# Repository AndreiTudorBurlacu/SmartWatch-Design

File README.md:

# Design Smartwatch

A smartwatch based on the Nordic nRF52840 microcontroller with an e-Paper display.
---

## Diagrama bloc

---

## Bill of Materials

| Ref | Componenta | Valoare | JLC Parts | Datasheet |
|-----|------------|---------|-----------|-----------|
| U1 | nRF52840 | $5.12   | [JLC](https://jlcpcb.com/parts/componentSearch?searchTxt=nRF52840-QF) | [DS](https://jlcpcb.com/api/file/downloadByFileSystemAccessId/8589839228197629952) |
| X1 | NX2016SA-32MHZ-EXS00A-CS11336 | $9.06   | [JLC](https://jlcpcb.com/partdetail/NDK-NX2016SA_32MHZ_EXS00ACS11336/C6134317) | [DS](https://jlcpcb.com/api/file/downloadByFileSystemAccessId/8603064888214908928) |
| X2 | FC-135_32.7680KA-A3 | $0.2923 | [JLC](https://jlcpcb.com/partdetail/SeikoEpson-FC_135_32_7680KAA3/C2650472) | [DS](https://jlcpcb.com/partdetail/SeikoEpson-FC_135_32_7680KAA3/C2650472) |
| L2 | RC0402JR-070RL | $0.02   | [JLC](https://jlcpcb.com/partdetail/YAGEO-RC0402JR070RL/C60485) | [DS](https://jlcpcb.com/api/file/downloadByFileSystemAccessId/8717146932348461056) |
| L3 | RC0402JR-070RL | $0.01   | [JLC](https://jlcpcb.com/partdetail/YAGEO-RC0402JR070RL/C60485) | [DS](https://jlcpcb.com/api/file/downloadByFileSystemAccessId/8717146932348461056) |
| L5 | 744043680 | $9.33   | [JLC](https://jlcpcb.com/partdetail/WurthElektronik-744043680/C2045671) | [DS](https://www.we-online.com/components/products/datasheet/744043680.pdf) |
| L7 | MLP2016SR47MT0S1 | $0.9    | [JLC](https://jlcpcb.com/partdetail/TDK-MLP2016SR47MT0S1/C87545) | [DS](https://jlcpcb.com/api/file/downloadByFileSystemAccessId/8588933367512879104) |
| IC1 | BQ25180YBGR | $2.04   | [JLC](https://jlcpcb.com/partdetail/TexasInstruments-BQ25180YBGR/C3682423) | [DS](https://www.ti.com/cn/lit/gpn/bq25180) |
| IC2 | DRV2605YZFR | $1.61   | [JLC](https://jlcpcb.com/partdetail/TexasInstruments-DRV2605YZFR/C81079) | [DS](https://www.ti.com/cn/lit/gpn/drv2605) |
| IC3 | BMA423 | $12.30  | [JLC](https://jlcpcb.com/partdetail/BoschSensortec-BMA423/C189517) | [DS](https://jlcpcb.com/api/file/downloadByFileSystemAccessId/8588894317147017216) |
| IC9 | RT6160 | $0.46   | [JLC](https://jlcpcb.com/partdetail/RichtekTech-RT6160AWSC/C7065276) | [DS](https://jlcpcb.com/api/file/downloadByFileSystemAccessId/8600398231234883584) |
| ANT1 | 2450AT18B100E | $1.04   | [JLC](https://jlcpcb.com/partdetail/JohansonDielectrics-2450AT18B100E/C2917717) | [DS](https://jlcpcb.com/api/file/downloadByFileSystemAccessId/8588940948130156544) |
| D2 | MBR0530 | $0.02   | [JLC](https://jlcpcb.com/partdetail/78464-MBR0530/C77336) | [DS](https://jlcpcb.com/api/file/downloadByFileSystemAccessId/8586175081181818880) |
| D3 | USBLC6-2SC6Y | $0.23   | [JLC](https://jlcpcb.com/partdetail/STMicroelectronics-USBLC62SC6Y/C2969755) | [DS](https://jlcpcb.com/api/file/downloadByFileSystemAccessId/8603165824304111616) |
| D4 | MBR0530 | $0.03   | [JLC](https://jlcpcb.com/partdetail/78464-MBR0530/C77336) | [DS](https://jlcpcb.com/api/file/downloadByFileSystemAccessId/8586175081181818880) |
| D5 | MBR0530 | $0.04   | [JLC](https://jlcpcb.com/partdetail/78464-MBR0530/C77336) | [DS](https://jlcpcb.com/api/file/downloadByFileSystemAccessId/8586175081181818880) |
| Q1 | DMG2305UX-7 | $0.15   | [JLC](https://jlcpcb.com/partdetail/DiodesIncorporated-DMG2305UX7/C150470) | [DS](https://jlcpcb.com/api/file/downloadByFileSystemAccessId/8560079443617075200) |
| Q3 | SI1308EDL-T1-GE3 | $0.15   | [JLC](https://jlcpcb.com/partdetail/VishayIntertech-SI1308EDL_T1GE3/C469327) | [DS](https://jlcpcb.com/api/file/downloadByFileSystemAccessId/8588884784742846464) |
| J1 | 503480-2400 | $0.67   | [JLC](https://jlcpcb.com/partdetail/MOLEX-5034802400/C122434) | [DS](https://www.molex.com/content/dam/molex/molex-dot-com/products/automated/en-us/salesdrawingpdf/503/503480/5034802400_sd.pdf?inline) |
| J4 | KH-TYPE-C-16P | $0.05   | [JLC](https://jlcpcb.com/partdetail/Shenzhen_KinghelmElec-KH_TYPE_C16P/C709357) | [DS](https://jlcpcb.com/api/file/downloadByFileSystemAccessId/8588905154556923904) |
| U3 | MAX17048G-T10 | $2.76   | [JLC](https://jlcpcb.com/partdetail/2777647-MAX17048GT10/C2682616) | [DS](https://jlcpcb.com/api/file/downloadByFileSystemAccessId/8588907428524003328) |
| SWD | TC2030-IDC | $101.26 | [JLC](https://jlcpcb.com/partdetail/MicrochipTech-TC2030_CLIP3PACK/C5444772) | [DS](https://www.lcsc.com/datasheet/lcsc_datasheet_2403201318_Microchip-Tech-TC2030-CLIP-3PACK_C5444772.pdf) |

---

## Descriere Functionalitati Hardware

### Microcontroller - nRF52840

Arhitectura:
- Procesor ARM Cortex-M4 cu FPU ruland la 64 MHz
- 1 MB memorie Flash si 256 KB RAM
- Suport nativ pentru Bluetooth 5, Bluetooth Low Energy (BLE), Thread si Zigbee
- Dispune de USB 2.0 (Full Speed), SPI, I2C, UART si QSPI
 
### Display E-Paper - Waveshare 1.54" V2
 
Display-ul comunica prin SPI pe 4 fire:
- Rezolutie: 200x200 pixeli
- Interfata comunicare: SPI
- Consum de energie ultra-redus; consuma aproximativ 26.4 mW doar in timpul reimprospatarii si scade sub 0.01 uA in modul standby
- Suporta partial refresh (reimprospatarea doar a unei anumite zone din ecran)
 
### IMU - BMA423
 
Accelerometrul BMA423 comunica prin I2C:

- Tip senzor: Accelerometru digital pe 3 axe.
- Rezolutie date - 12 biti
- Interfete comunicare: I2C si SPI
- Consum foarte eficient, trage in jur de 14 uA cand se afla in modul activ de numarare a pasilor
 
### Incarcator Baterie - BQ25180

- Dimensiuni: 32.5mm x 21mm x 5.5mm
- Curent de incarcare: Flexibil, poate incarca de la cativa miliamperi pana la 1 A
- Interfata control: Comunicare I2C prin care procesorul principal poate citi statusul bateriei si poate modifica parametrii de incarcare din mers
- Tensiune standard de intrare de 5V, dar are protectie la supratensiune (OVP) care rezista pana la 25V
 
### Baterie - AKYGA LP502030
 
- Tensiune - 3.7V nominal (ajunge la 4.2V cand este incarcata 100% si scade spre 3.0V cand este descarcata)
- Capacitate: Aproximativ 250 mAh
- Dimensiuni - 5 mm x 20 mm x 30 mm
 
### Motor Vibratii - FIT0774

- Tensiune de operare: 3V curent continuu
- Curent maxim consumat - 85 mA in momentul in care vibreaza la capacitate maxima
- Viteza de rotatie: Aproximativ 12000 RPM
- 10 mm diametru si o grosime de doar 2.7 mm
 
### Conector Debug - TC2030-IDC
 
- Tip contact: 6 pini cu arc (pogo-pins) dispusi pe 2 randuri, cu o distanta de 1.27 mm intre ei
- Folosit pentru programare si debugging SWD
- Semnale: SWDIO, SWDCLK, GND, VCC, RESET
 
---
 
## Pinii nRF52840
 
| Pin nRF52840 | Semnal | Componenta | Interfata |
|--------------|--------|-----------|-----------|
| P0.00/XL1 | XL1 | Crystal X2 (32.768kHz) | XTAL |
| P0.01/XL2 | XL2 | Crystal X2 (32.768kHz) | XTAL |
| P0.05/AIN3 | EPD_CS | E-Paper (J1 FPC) | SPI CS |
| P0.06 | SDA | BMA423, BQ25180, MAX17048, DRV2605 | I2C SDA |
| P0.07 | SCL | BMA423, BQ25180, MAX17048, DRV2605 | I2C SCL |
| P0.08 | IMU_INT1 | BMA423 | GPIO Input |
| P1.08 | IMU_INT2 | BMA423 | GPIO Input |
| P0.11 | PMIC_INT | BQ25180 | GPIO Input |
| P0.12 | HAPTIC_EN | DRV2605 | GPIO |
| VBUS | VBUS | USB-C (J4) | Power |
| D- | D- | USB-C (J4) / USBLC6 | USB |
| D+ | D+ | USB-C (J4) / USBLC6 | USB |
| P0.13 | SW_UP | Buton Up | GPIO Input |
| P0.14 | SW_ENT | Buton Enter | GPIO Input |
| P0.15 | EPD_DC | E-Paper (J1 FPC) | SPI DC |
| P0.16 | EPD_RST | E-Paper (J1 FPC) | GPIO |
| P0.17 | EPD_BUSY | E-Paper (J1 FPC) | GPIO Input |
| P0.18/RESET | RESET | TC2030-IDC | SWD/GPIO |
| SWDCLK | SWDCLK | TC2030-IDC | SWD |
| SWDIO | SWDIO | TC2030-IDC | SWD |
| P1.02 | SW_DN | Buton Down | GPIO Input |
| P0.10/NFC2 | ALERT | MAX17048 | GPIO Input |
| ANT | RF | Antena 2450AT18B100E | RF |
| P0.02/AIN0 | SCK | E-Paper (J1 FPC) | SPI SCK |
| P0.03/AIN1 | MOSI | E-Paper (J1 FPC) | SPI MOSI |

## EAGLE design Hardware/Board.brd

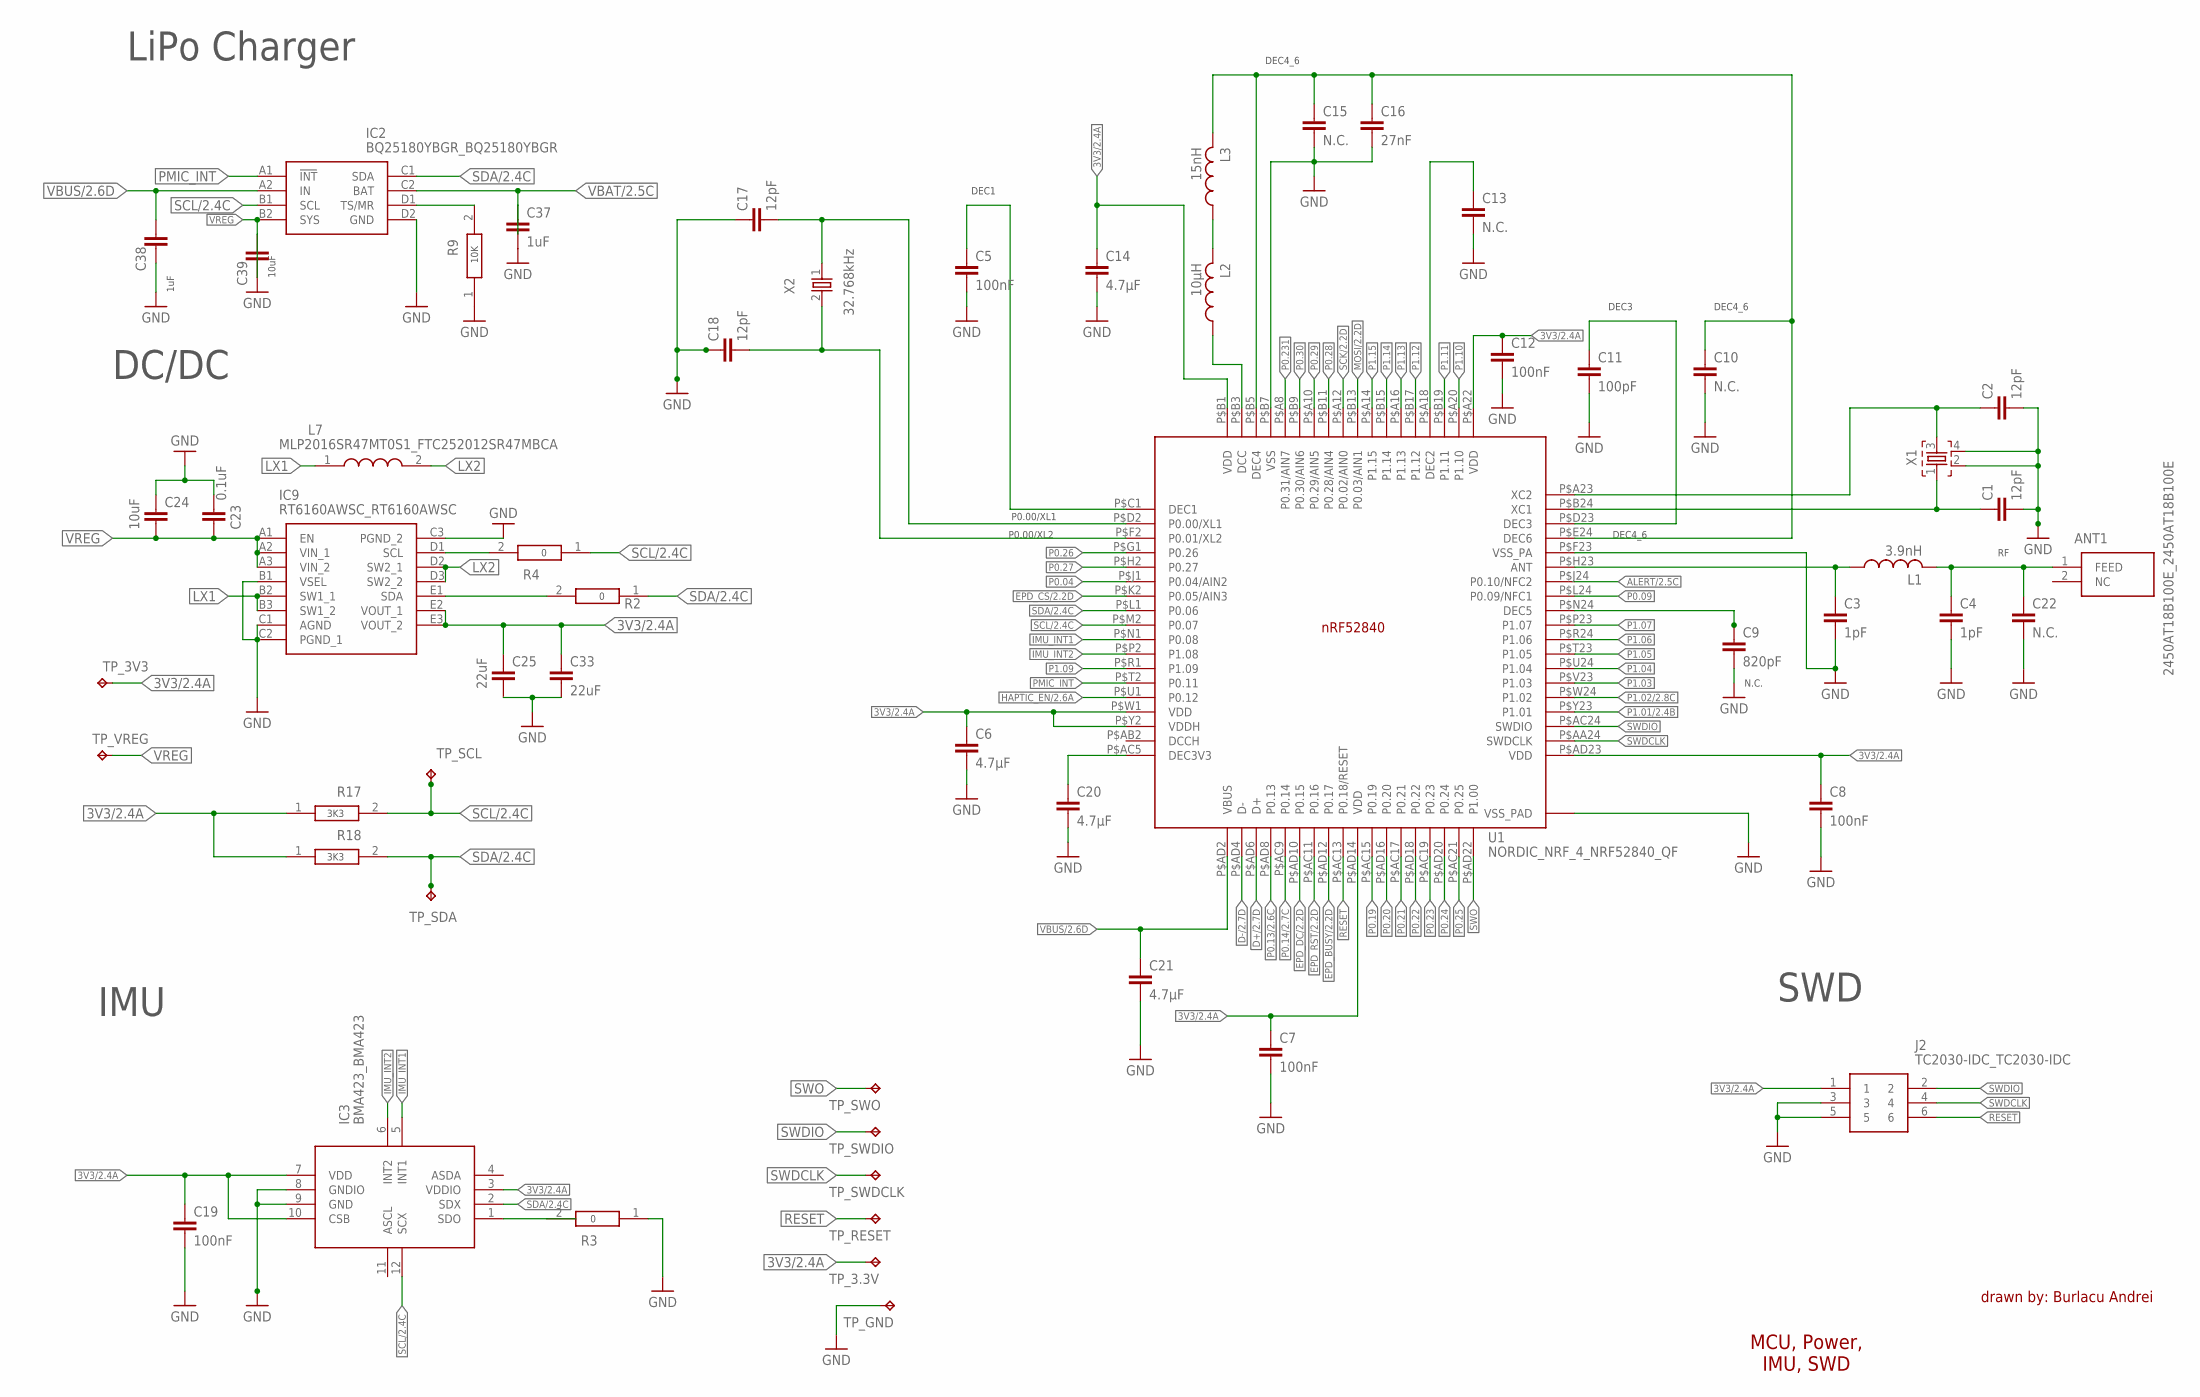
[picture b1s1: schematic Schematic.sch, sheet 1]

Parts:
ANT1: 2450AT18B100E_2450AT18B100E; 2450AT18B100E_ANTC3216X140N
C1, C2, C17, C18: 12pF; NORDIC_NRF_3_RESC0201_L
C3, C4: 1pF; NORDIC_NRF_3_RESC0201_L
C5, C7, C8, C12, C19: 100nF; NORDIC_NRF_3_RESC0201_L
C6, C14, C20, C21: 4.7µF; NORDIC_NRF_3_RESC0201_L
C9: 820pF; NORDIC_NRF_3_RESC0201_L
C10, C13, C15, C22: N.C.; NORDIC_NRF_3_RESC0201_L
C11: 100pF; NORDIC_NRF_3_RESC0201_L
C16: 27nF; NORDIC_NRF_3_RESC0201_L
C23: 0.1uF; NORDIC_NRF_3_RESC0201_L
C24: 10uF; NORDIC_NRF_3_RESC0201_L
C25, C33: 22uF; NORDIC_NRF_3_RESC0201_L
C37: 1uF; NORDIC_NRF_3_RESC0201_L
C38, C39: NORDIC_NRF_3_CAPACITOR_0201_L; NORDIC_NRF_3_RESC0201_L
IC2: BQ25180YBGR_BQ25180YBGR; BQ25180YBGR_BGA8C40P2X4_100X155X50
IC3: BMA423_BMA423
IC9: RT6160AWSC_RT6160AWSC; RT6160AWSC_BGA15C40P3X5_140X230X60
J2: TC2030-IDC_TC2030-IDC; TC2030-IDC_TC2030IDC
L1: 3.9nH; NORDIC_NRF_2_RESC0402_L
L2: 10µH; NORDIC_NRF_2_RESC0402_L
L3: 15nH; NORDIC_NRF_2_RESC0402_L
L7: MLP2016SR47MT0S1_FTC252012SR47MBCA; MLP2016SR47MT0S1_INDC2016X100N
R2, R3, R4, R9, R17, R18: ERA-1AEB3401C_CPF0201D7K68C1; ERA-1AEB3401C_0201
TP_3.3V, TP_3V3: HECTOR_WATCH_1_TPTP20R; HECTOR_WATCH_1_TP20R
TP_GND: HECTOR_WATCH_1_TPTP20R; HECTOR_WATCH_1_TP20R
TP_RESET: HECTOR_WATCH_1_TPTP20R; HECTOR_WATCH_1_TP20R
TP_SCL: HECTOR_WATCH_1_TPTP20R; HECTOR_WATCH_1_TP20R
TP_SDA: HECTOR_WATCH_1_TPTP20R; HECTOR_WATCH_1_TP20R
TP_SWDCLK: HECTOR_WATCH_1_TPTP20R; HECTOR_WATCH_1_TP20R
TP_SWDIO: HECTOR_WATCH_1_TPTP20R; HECTOR_WATCH_1_TP20R
TP_SWO: HECTOR_WATCH_1_TPTP20R; HECTOR_WATCH_1_TP20R
TP_VREG: HECTOR_WATCH_1_TPTP20R; HECTOR_WATCH_1_TP20R
U1: NORDIC_NRF_4_NRF52840_QF; NORDIC_NRF_4_AQFN50P700X700X85_HS-74N
X1: NORDIC_NRF_XTAL_32MHZ; NORDIC_NRF_BT-XTAL_2016_N
X2: 32.768kHz; NORDIC_NRF_1_XTAL_3215_N

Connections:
GND: C3.2, C4.2, C5.2, C6.2, C7.2, C8.2, C9.2, C10.2, C11.2, C12.2, C13.2, C14.2, C15.2, C16.2, C19.2, C20.2, C21.2, C22.2, C23.1, C24.1, C25.2, C33.2, C37.2, C38.2, C39.1, C39.2, IC2.B2 (SYS), IC2.D2 (GND), IC9.B1 (VSEL), IC9.C1 (AGND), IC9.C2 (PGND_1), IC9.C3 (PGND_2), J2.3, J2.5, R3.1, R9.1, TP_GND.TP, U1.P$74 (VSS_PAD), U1.P$75 (VSS_PAD), U1.P$76 (VSS_PAD), U1.P$77 (VSS_PAD), U1.P$78 (VSS_PAD), U1.P$79 (VSS_PAD), U1.P$80 (VSS_PAD), U1.P$81 (VSS_PAD), U1.P$82 (VSS_PAD), U1.P$83 (VSS_PAD), U1.P$84 (VSS_PAD), U1.P$85 (VSS_PAD), U1.P$86 (VSS_PAD), U1.P$87 (VSS_PAD), U1.P$88 (VSS_PAD), U1.P$89 (VSS_PAD), U1.P$90 (VSS_PAD), U1.P$B7 (VSS), U1.P$F23 (VSS_PA); also elsewhere on the board
unnamed: IC2.D1 (TS/MR), R9.2
unnamed: C38.1, IC2.A2 (IN)
unnamed: C37.1, IC2.C2 (BAT)
unnamed: C23.2, C24.2, IC9.A1 (EN), IC9.A2 (VIN_1), IC9.A3 (VIN_2)
unnamed: IC9.B2 (SW1_1), IC9.B3 (SW1_2)
unnamed: IC9.D1 (SCL), R4.2
unnamed: R17.1, R18.1
unnamed: IC9.D2 (SW2_1), IC9.D3 (SW2_2)
unnamed: C25.1, C33.1, IC9.E2 (VOUT_1), IC9.E3 (VOUT_2)
unnamed: IC9.E1 (SDA), R2.2
unnamed: C19.1, IC3.7 (VDD), IC3.10 (CSB)
unnamed: IC3.8 (GNDIO), IC3.9 (GND)
unnamed: IC3.1 (SDO), R3.2
unnamed: C7.1, U1.P$AD14 (VDD)
unnamed: C21.1, U1.P$AD2 (VBUS)
unnamed: C8.1, U1.P$AD23 (VDD)
unnamed: C3.1, L1.1, U1.P$H23 (ANT)
unnamed: ANT1.1 (FEED), C4.1, C22.1, L1.2
unnamed: C10.1, C15.1, C16.1, L3.2, U1.P$B5 (DEC4), U1.P$E24 (DEC6)
unnamed: C11.1, U1.P$D23 (DEC3)
unnamed: C1.1, U1.P$B24 (XC1), X1.1
unnamed: C2.1, U1.P$A23 (XC2), X1.3
unnamed: C1.2, C2.2, X1.2, X1.4
unnamed: C12.1, U1.P$A22 (VDD)
unnamed: C13.1, U1.P$A18 (DEC2)
unnamed: L2.2, L3.1
unnamed: L2.1, U1.P$B3 (DCC)
unnamed: C20.1, U1.P$AC5 (DEC3V3)
unnamed: C6.1, U1.P$W1 (VDD), U1.P$Y2 (VDDH)
unnamed: C14.1, U1.P$B1 (VDD)
unnamed: C5.1, U1.P$C1 (DEC1)
unnamed: C17.2, U1.P$D2 (P0.00/XL1), X2.1
unnamed: C18.2, U1.P$F2 (P0.01/XL2), X2.2
SDA/2.4C: IC2.C1 (SDA)

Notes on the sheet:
LiPo Charger
10K
DC/DC
3K3
10uF
1uF
IMU
N.C.
DEC3
DEC4_6
DEC1
P0.00/XL1
P0.00/XL2
drawn by: Burlacu Andrei
MCU, Power, IMU, SWD
SWD

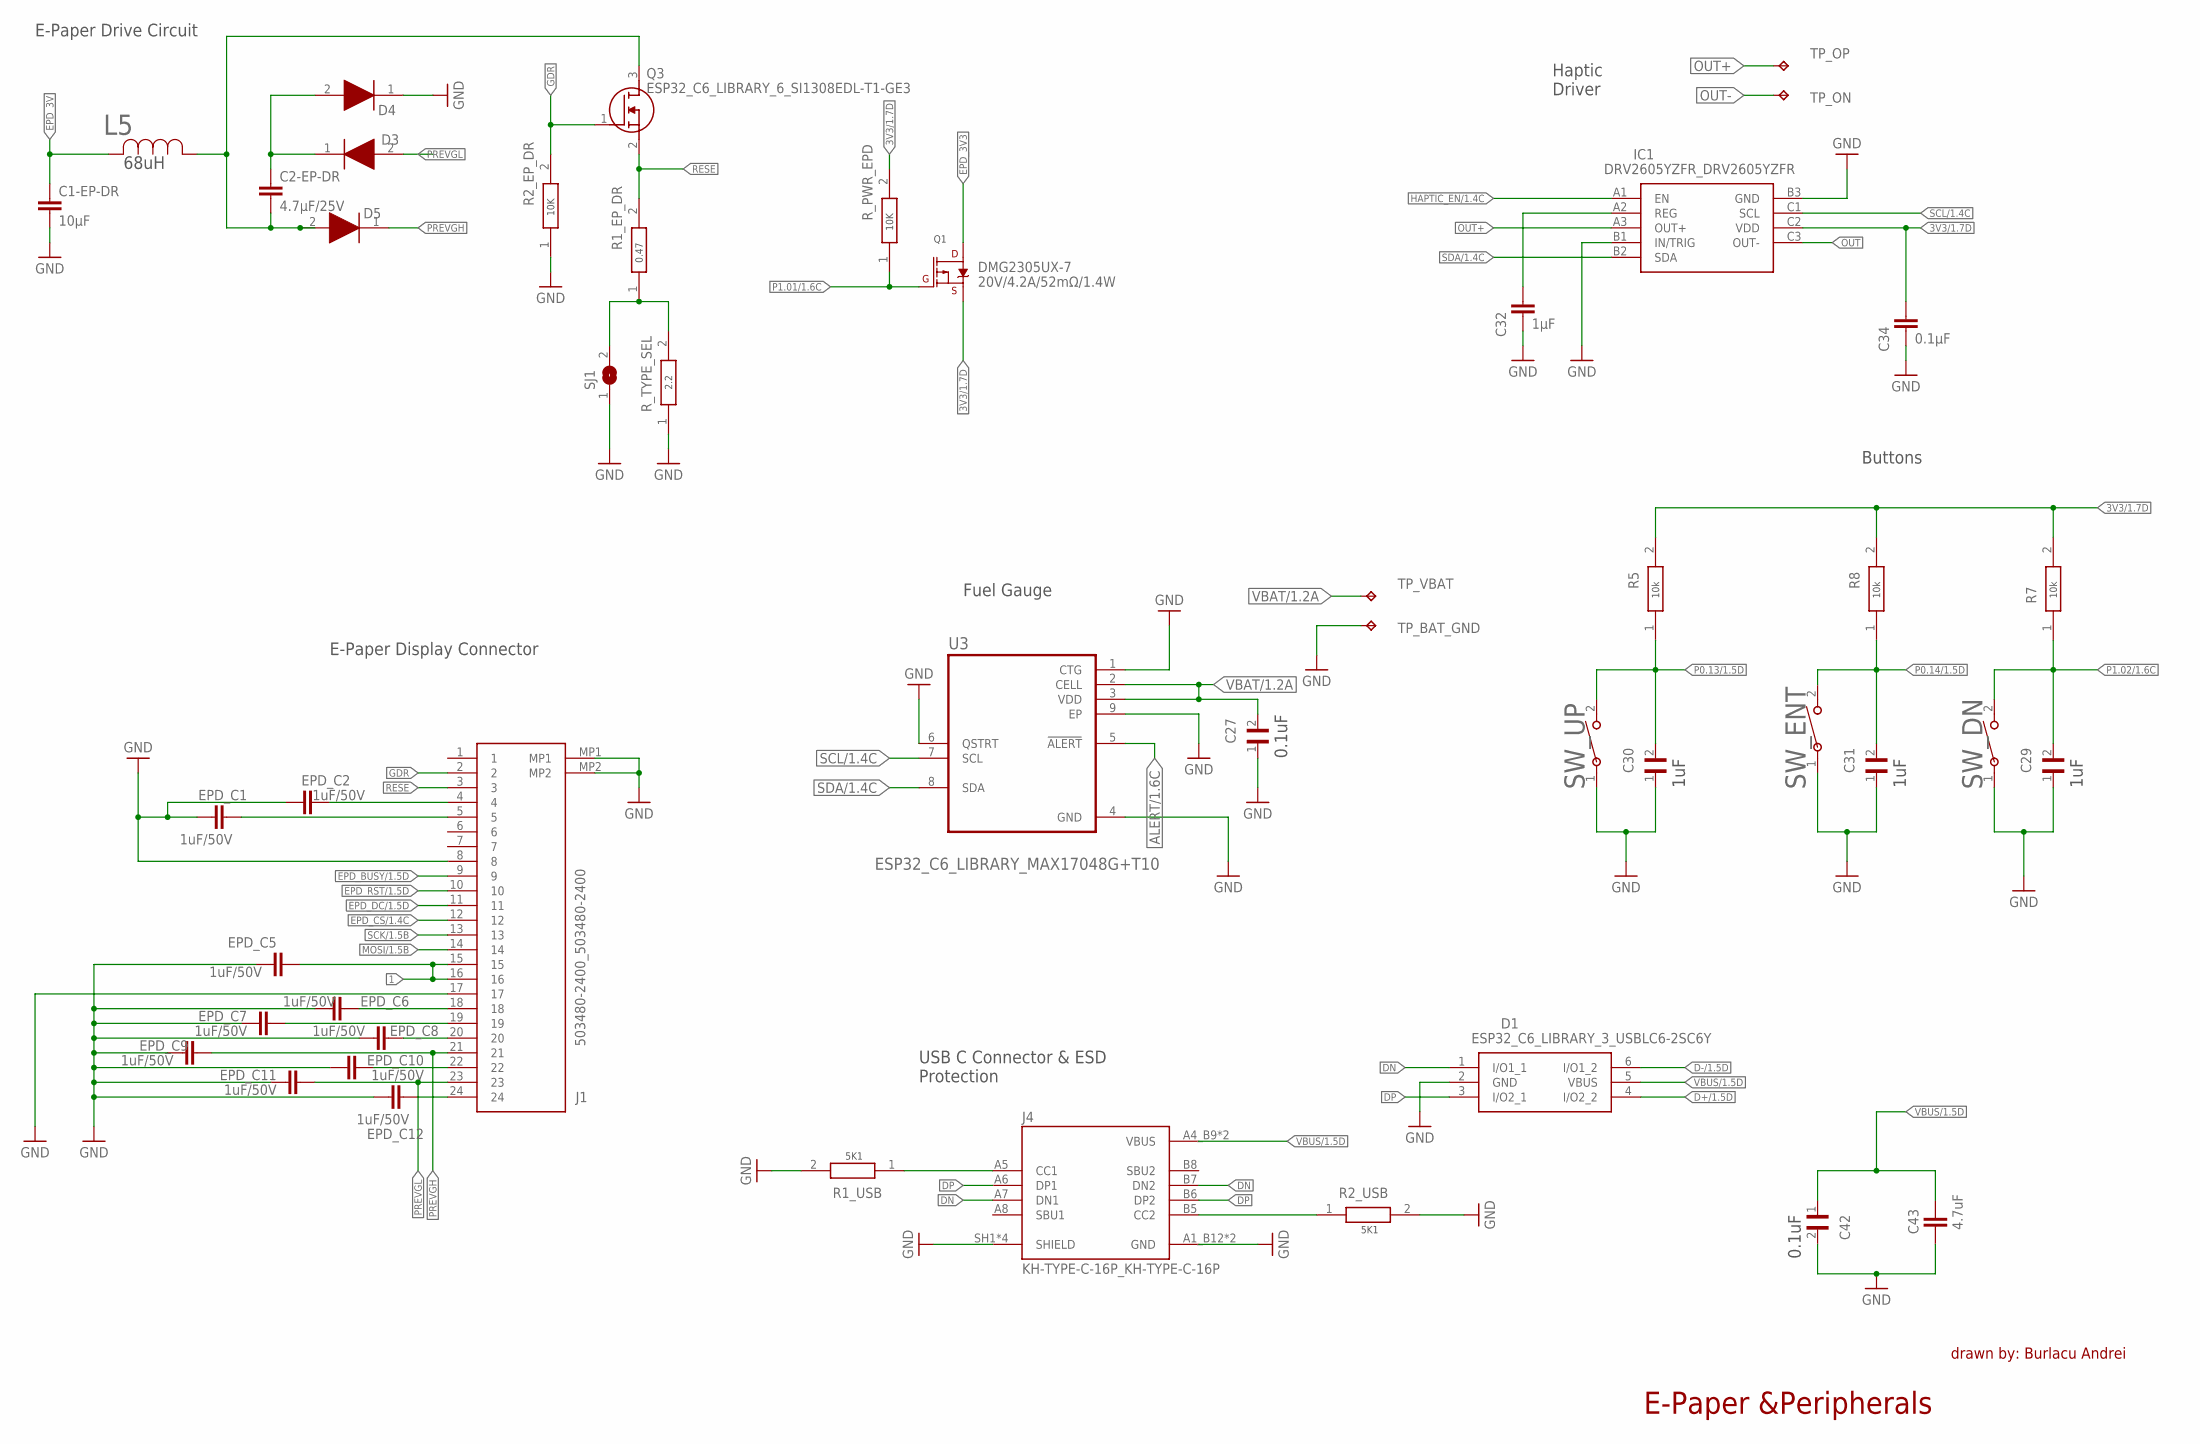
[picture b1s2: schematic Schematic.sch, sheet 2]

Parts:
C1-EP-DR: 10µF; NORDIC_NRF_3_RESC0201_L
C2-EP-DR: 4.7µF/25V; NORDIC_NRF_3_RESC0201_L
C27, C29, C30, C31, C42: GRM011R60J152KE01L_2_GRM011R60J152KE01L; GRM011R60J152KE01L_2_CAPC0201X13N
C32: 1µF; NORDIC_NRF_3_RESC0201_L
C34: 0.1µF; NORDIC_NRF_3_RESC0201_L
C43: 4.7uF; NORDIC_NRF_3_RESC0201_L
D1: ESP32_C6_LIBRARY_3_USBLC6-2SC6Y; ESP32_C6_LIBRARY_3_SOT95P280X145-6N
D3, D4, D5: ESP32_C6_LIBRARY_5_MBR0530; ESP32_C6_LIBRARY_5_SOD3716X135N
DMG2305UX-7: 20V/4.2A/52mΩ/1.4W; ESP32_C6_LIBRARY_4_ESP32_C6_LIBRARY_4_ESP32_C6_LIBRARY_4_ES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
EPD_C1, EPD_C2, EPD_C5, EPD_C6, EPD_C7, EPD_C8, EPD_C9, EPD_C10, EPD_C11, EPD_C12: 1uF/50V; NORDIC_NRF_3_RESC0201_L
IC1: DRV2605YZFR_DRV2605YZFR; DRV2605YZFR_BGA9C50P3X3_144X144X62
J1: 503480-2400_503480-2400; 503480-2400_5034802400
J4: KH-TYPE-C-16P_KH-TYPE-C-16P; KH-TYPE-C-16P_KINGHELM_KH-TYPE-C-16P
L5: 68uH; ESP32_C6_LIBRARY_2_IND_4828-WE-TPC_WRE
Q3: ESP32_C6_LIBRARY_6_SI1308EDL-T1-GE3; ESP32_C6_LIBRARY_6_SOT65P210X110-3N
R1_EP_DR, R1_USB, R2_EP_DR, R2_USB, R5, R7, R8: ERA-1AEB3401C_CPF0201D7K68C1; ERA-1AEB3401C_0201
R_PWR_EPD: ERA-1AEB3401C_CPF0201D7K68C1; ERA-1AEB3401C_0201
R_TYPE_SEL: ERA-1AEB3401C_CPF0201D7K68C1; ERA-1AEB3401C_0201
SJ1: ESP32_C6_LIBRARY_7_JUMPER_SJ
SW_DN: 2025-10-22_07-23-44_LIBRARY_EVP-AKE31ASW_EVP-AKE3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; 2025-10-22_07-23-44_LIBRARY_SW_EVP-AKE31A_PAN
SW_ENT: 2025-10-22_07-23-44_LIBRARY_EVP-AKE31ASW_EVP-AKE3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; 2025-10-22_07-23-44_LIBRARY_SW_EVP-AKE31A_PAN
SW_UP: 2025-10-22_07-23-44_LIBRARY_EVP-AKE31ASW_EVP-AKE3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; 2025-10-22_07-23-44_LIBRARY_SW_EVP-AKE31A_PAN
TP_BAT_GND: HECTOR_WATCH_1_TPTP20R; HECTOR_WATCH_1_TP20R
TP_ON: HECTOR_WATCH_1_TPTP20R; HECTOR_WATCH_1_TP20R
TP_OP: HECTOR_WATCH_1_TPTP20R; HECTOR_WATCH_1_TP20R
TP_VBAT: HECTOR_WATCH_1_TPTP20R; HECTOR_WATCH_1_TP20R
U3: ESP32_C6_LIBRARY_MAX17048G+T10; ESP32_C6_LIBRARY_SON50P200X200X80-9N

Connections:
GND: C1-EP-DR.2, C27.1, C29.1, C30.1, C31.1, C32.2, C34.2, D1.2 (GND), D4.1 (K), EPD_C1.1, EPD_C2.1, EPD_C5.1, EPD_C6.1, EPD_C7.1, EPD_C8.1, EPD_C9.1, EPD_C10.1, EPD_C11.1, EPD_C12.1, IC1.B1 (IN/TRIG), IC1.B3 (GND), J1.8, J1.17, J1.MP1, J1.MP2, J4.A1_B12 (GND), J4.A12_B1 (GND), J4.SH1 (SHIELD), J4.SH2 (SHIELD), J4.SH3 (SHIELD), J4.SH4 (SHIELD), R1_USB.2, R2_EP_DR.1, R2_USB.2, R_TYPE_SEL.1, SJ1.1, SW_DN.1, SW_ENT.1, SW_UP.1, TP_BAT_GND.TP, U3.1 (CTG), U3.4 (GND), U3.6 (QSTRT), U3.9 (EP); also elsewhere on the board
GND1: R1_EP_DR.1, R_TYPE_SEL.2, SJ1.2
GND2: C29.2, R7.1, SW_DN.2
GND3: C31.2, R8.1, SW_ENT.2
GND4: C30.2, R5.1, SW_UP.2
unnamed: C1-EP-DR.1, L5.2
unnamed: C2-EP-DR.2, D5.2 (A), L5.1, Q3.3 (D)
unnamed: C2-EP-DR.1, D3.1 (K), D4.2 (A)
unnamed: Q3.1 (G), R2_EP_DR.2
unnamed: Q3.2 (S), R1_EP_DR.2
unnamed: DMG2305UX-7.1 (G), R_PWR_EPD.1
unnamed: C32.1, IC1.A2 (REG)
unnamed: C34.1, IC1.C2 (VDD)
unnamed: R5.2, R7.2, R8.2
unnamed: C27.2, U3.2 (CELL), U3.3 (VDD)
unnamed: EPD_C12.2, J1.24
unnamed: EPD_C2.2, J1.4
unnamed: EPD_C1.2, J1.5
unnamed: EPD_C5.2, J1.15, J1.16
unnamed: EPD_C11.2, J1.23
unnamed: EPD_C10.2, J1.22
unnamed: EPD_C9.2, J1.21
unnamed: EPD_C8.2, J1.20
unnamed: EPD_C7.2, J1.19
unnamed: EPD_C6.2, J1.18
unnamed: J4.A4_B9 (VBUS), J4.A9_B4 (VBUS)
unnamed: J4.B5 (CC2), R2_USB.1
unnamed: J4.A5 (CC1), R1_USB.1
unnamed: C42.2, C43.1
unnamed: C42.1, C43.2

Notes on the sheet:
E-Paper Drive Circuit
10K
0.47
2.2
68uH
Haptic Driver
Buttons
10k
1uF
Fuel Gauge
0.1uF
E-Paper Display Connector
USB C Connector & ESD Protection
5K1
E-Paper &Peripherals
drawn by: Burlacu Andrei

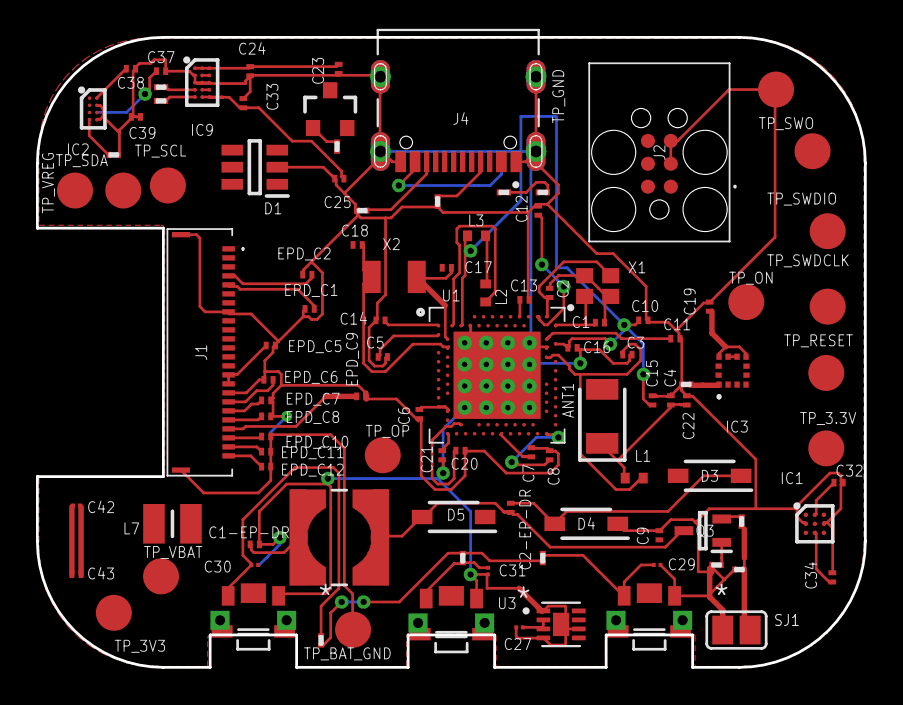
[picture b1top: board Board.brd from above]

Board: 2 copper layers, 46.0 x 35.0 mm, 105 parts (0 on the bottom side), 63 nets.

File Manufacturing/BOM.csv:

Reference Designators;Quantity;Description;Package;Value;Manufacturer;Manufacturer Part Number;Vendor;Vendor Part Number;Top/Bottom;
;1;PCB Board;Board;;;;;;;
ANT1;1;Antennas 2.45GHz ANTENNA;2450AT18B100E_ANTC3216X140N;2450AT18B100E_2450AT18B100E;;;;;Top;
C1, C2, C17, C18;4;Generic chip capacitor;NORDIC_NRF_3_RESC0201_L;12pF;;;;;Top;
C1-EP-DR;1;Generic chip capacitor;NORDIC_NRF_3_RESC0201_L;10µF;;;;;Top;
C2-EP-DR;1;Generic chip capacitor;NORDIC_NRF_3_RESC0201_L;4.7µF/25V;;;;;Top;
C3, C4;2;Generic chip capacitor;NORDIC_NRF_3_RESC0201_L;1pF;;;;;Top;
C5, C7, C8, C12, C19;5;Generic chip capacitor;NORDIC_NRF_3_RESC0201_L;100nF;;;;;Top;
C6, C14, C20, C21;4;Generic chip capacitor;NORDIC_NRF_3_RESC0201_L;4.7µF;;;;;Top;
C9;1;Generic chip capacitor;NORDIC_NRF_3_RESC0201_L;820pF;;;;;Top;
C10, C13, C15, C22;4;Generic chip capacitor;NORDIC_NRF_3_RESC0201_L;N.C.;;;;;Top;
C11;1;Generic chip capacitor;NORDIC_NRF_3_RESC0201_L;100pF;;;;;Top;
C16;1;Generic chip capacitor;NORDIC_NRF_3_RESC0201_L;27nF;;;;;Top;
C23;1;Generic chip capacitor;NORDIC_NRF_3_RESC0201_L;0.1uF;;;;;Top;
C24;1;Generic chip capacitor;NORDIC_NRF_3_RESC0201_L;10uF;;;;;Top;
C25, C33;2;Generic chip capacitor;NORDIC_NRF_3_RESC0201_L;22uF;;;;;Top;
C27, C29, C30, C31, C42;5;Check availability;CAPC0201X13N;GRM011R60J152KE01L_2_GRM011R60J152KE01L;;;;;Top;
C32;1;Generic chip capacitor;NORDIC_NRF_3_RESC0201_L;1µF;;;;;Top;
C34;1;Generic chip capacitor;NORDIC_NRF_3_RESC0201_L;0.1µF;;;;;Top;
C37, C38, C39;3;Generic chip capacitor;NORDIC_NRF_3_RESC0201_L;;;;;;Top;
C43;1;Generic chip capacitor;NORDIC_NRF_3_RESC0201_L;4.7uF ;;;;;Top;
D1;1;Low Cap. ESD Protection Auto SOT-23-6 STMicroelectronics USBLC6-2SC6Y, Dual Uni-Directional TVS Diode Array, 6-Pin SOT-23;SOT95P280X145-6N;ESP32_C6_LIBRARY_3_USBLC6-2SC6Y;;;;;Top;
D3, D4, D5;3;ON SEMICONDUCTOR - MBR0530 - DIODE, SCHOTTKY, 0.5A, 30V, SOD-123;SOD3716X135N;ESP32_C6_LIBRARY_5_MBR0530;;;;;Top;
DMG2305UX-7;1;P-channel MOSFETs;ESP32_WROVER_SPARKFUN-DISCRETESEMI_SOT23-3;20V/4.2A/52mΩ/1.4W;;;;;Top;
EPD_C1, EPD_C2;2;Generic chip capacitor;NORDIC_NRF_3_RESC0201_L;1uF/50V ;;;;;Top;
EPD_C5, EPD_C6, EPD_C7, EPD_C8, EPD_C9, EPD_C10, EPD_C11, EPD_C12;8;Generic chip capacitor;NORDIC_NRF_3_RESC0201_L;0.1uF/50V;;;;;Top;
IC1;1;Haptic Driver for ERM/LRA with Built-In Library and Smart Loop Architecture;DRV2605YZFR_BGA9C50P3X3_144X144X62;DRV2605YZFR_DRV2605YZFR;;;;;Top;
IC2;1;Charger IC Lithium Ion/Polymer, Lithium Iron Phosphate 8-DSBGA (1.6x1.1);BQ25180YBGR_BGA8C40P2X4_100X155X50;BQ25180YBGR_BQ25180YBGR;;;;;Top;
IC3;1;Accelerometers Triaxial low-g 12bit Acceleration Sensor;BMA423_BMA423;BMA423_BMA423;;;;;Top;
IC9;1;Buck-Boost Regulator Positive Output Step-Up/Step-Down I2C DC-DC Controller IC 15-WL-CSP (BSC) (1.4x2.3);RT6160AWSC_BGA15C40P3X5_140X230X60;RT6160AWSC_RT6160AWSC;;;;;Top;
J1;1;FFC & FPC Connectors 0.5mm FPC RA SMT Dual Contact 24Ckt;503480-2400_5034802400;503480-2400_503480-2400;;;;;Top;
J2;1;CABLE ADAPTER 6 POS;TC2030-IDC_TC2030IDC;TC2030-IDC_TC2030-IDC;;;;;Top;
J4;1;Check availability;KINGHELM_KH-TYPE-C-16P;KH-TYPE-C-16P_KH-TYPE-C-16P;;;;;Top;
L1;1;Generic chip inductor;NORDIC_NRF_2_RESC0402_L;3.9nH;;;;;Top;
L2;1;Generic chip inductor;NORDIC_NRF_2_RESC0402_L;10µH;;;;;Top;
L3;1;Generic chip inductor;NORDIC_NRF_2_RESC0402_L;15nH;;;;;Top;
L5;1;;ESP32_C6_LIBRARY_2_IND_4828-WE-TPC_WRE;68uH;;;;;Top;
L7;1;SMD / SMT Inductors (Coils), L=0.47?H, L x W x T :;MLP2016SR47MT0S1_INDC2016X100N;MLP2016SR47MT0S1_FTC252012SR47MBCA;;;;;Top;
Q3;1;MOSFET N-Ch 30V 1.5A TrenchFET SC70 Vishay Si1308EDL-T1-GE3 N-channel MOSFET Transistor, 1.5 A, 30 V, 3-Pin SC-70;SOT65P210X110-3N;ESP32_C6_LIBRARY_6_SI1308EDL-T1-GE3;;;;;Top;
R_PWR_EPD, R_TYPE_SEL, R1_EP_DR, R1_USB, R2, R2_EP_DR, R2_USB, R3, R4, R5, R7, R8, R9, R17, R18;15;7.68k 0201 Thin Film Surface Mount Fixed Resistor +/-0.5% 0.031W CPF0201D7K68C1;R0201;ERA-1AEB3401C_CPF0201D7K68C1;;;;;Top;
SJ1;1;SMD solder JUMPER;JUMPER_SJ;;;;;;Top;
SW_DN, SW_ENT, SW_UP;3;;SW_EVP-AKE31A_PAN;2025-10-22_07-23-44_LIBRARY_EVP-AKE31ASW_EVP-AKE31A_PAN;;;;;Top;
TP_3.3V, TP_3V3, TP_BAT_GND, TP_GND, TP_ON, TP_OP, TP_RESET, TP_SCL, TP_SDA, TP_SWDCLK, TP_SWDIO, TP_SWO, TP_VBAT, TP_VREG;14;Test pad;HECTOR_WATCH_1_TP20R;HECTOR_WATCH_1_TPTP20R;;;;;Top;
U1;1;nRF52840;NORDIC_NRF_4_AQFN50P700X700X85_HS-74N;NORDIC_NRF_4_NRF52840_QF;;;;;Top;
U3;1;Check availability;SON50P200X200X80-9N;ESP32_C6_LIBRARY_MAX17048G+T10;;;;;Top;
X1;1;;NORDIC_NRF_BT-XTAL_2016_N;;;;;;Top;
X2;1;;NORDIC_NRF_1_XTAL_3215_N;32.768kHz;;;;;Top;

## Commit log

2026-04-18 fixed review

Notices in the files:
parts and their libraries:
COPYRIGHT: Copyright (C) 2024 Ultra Librarian. All rights reserved.
COPYRIGHT: Copyright (C) 2025 Ultra Librarian. All rights reserved.
